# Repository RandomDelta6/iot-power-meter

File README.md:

# Iot Enabled Power Meter
Client server model for real-time monitoring of power usage aimed to simplify and modernise power usage readings and subsequent billing. Server backend handled by Firebase and Frontend made as a dynamic web app with angular framework. This project aims to elevate the process of power metering to modern connected standards and is primarily aimed towards power utility companies such that they may modernise their metering devices and enable them to be connected to the internet, allowing realtime monitoring and other advanced features like automated billing, remote disconnection, power outage detection and much more!  
The primary focus points of this project is simplicity, ease of installation of module, cost efficiency and rich user experience. 

## Documentation:
Slideshow presentation of the project highlighting the prominent topics discussed is available [here](https://docs.google.com/presentation/d/1crQ9AChwzRSzLb8-jiRmHGEgWye28_40_jXuga4SWwA/edit?usp=sharing).  
The [documentation](https://docs.google.com/document/d/1vDl4VJHqPTy9oJ1By9j4uT5io9Db-l0d9iFhtp2ZmS8/edit?usp=sharing) for the research conducted and subsequent issues addressed has been made available.  
[Dataflow logic](https://whimsical.com/data-flow-XnRbm9PbMYaVgHn5g6pd81) and [Firmware Algorithm Logic](https://whimsical.com/firmware-algorithm-PJ4HBDd6Cb4NwG5o3SaENn) flowcharts are also provided.  
Short Infographic video showcasing the project and primary discussion points is available [here](https://www.youtube.com/watch?v=jMkZ5F2Xh4k).

## Folder Structure:
```
./
  |-- power-iot-meter-fe (the frontend dashboard)
  --- power-iot-meter-hw (the firmware sketch)
```

## Frontend Preview

## Tools used:
- Angular
- Platform IO
- Espressif ESP32
- Arduino Framework
- Firebase RTDB
- Firebase Auth
- KiCAD

## Languages Used: 
- C/C++
- JS/TS

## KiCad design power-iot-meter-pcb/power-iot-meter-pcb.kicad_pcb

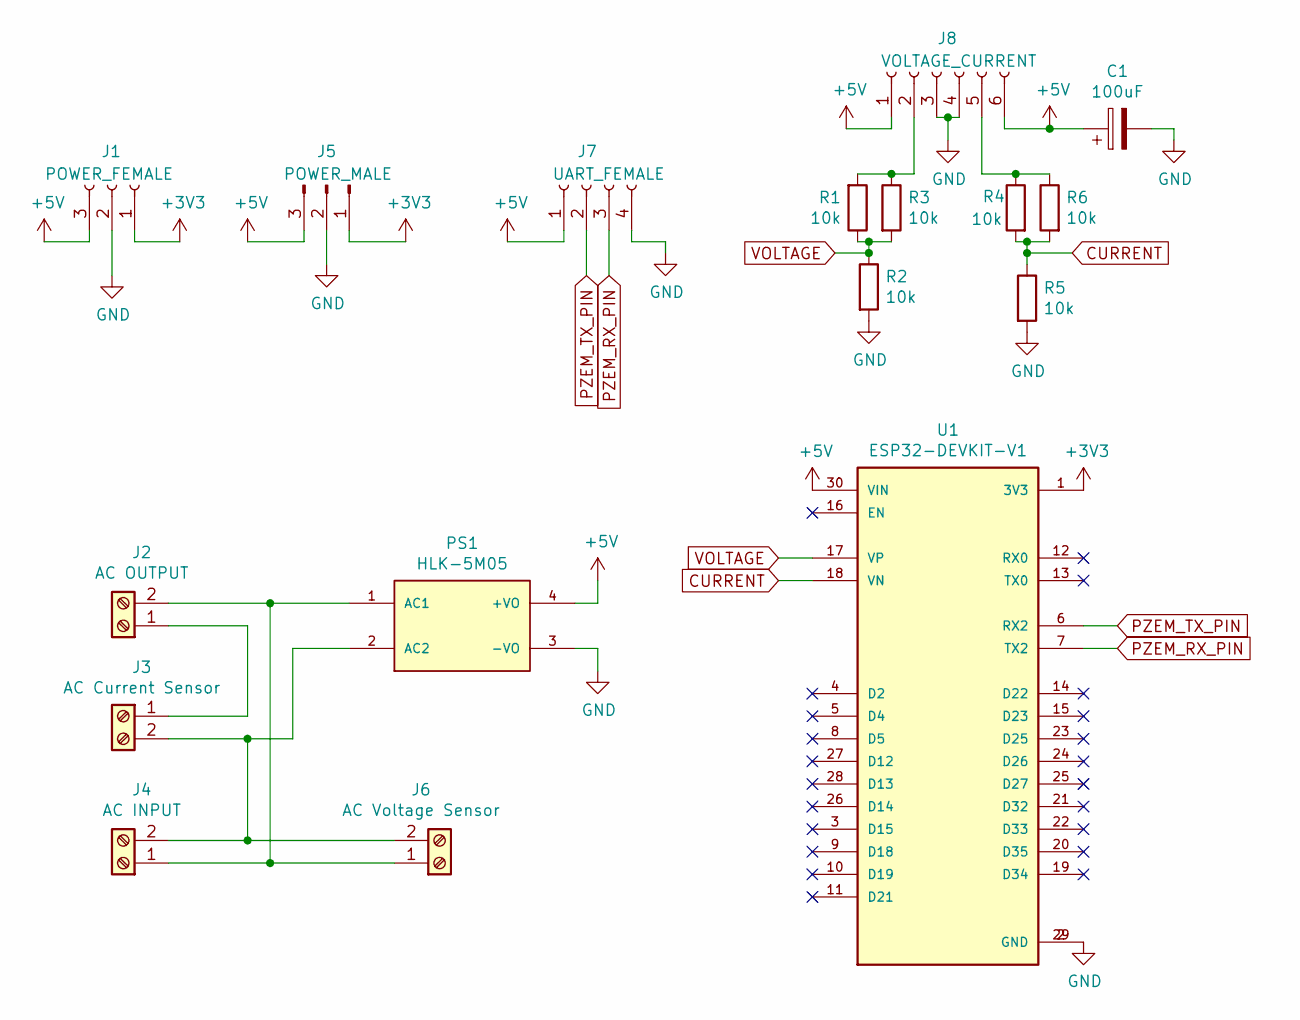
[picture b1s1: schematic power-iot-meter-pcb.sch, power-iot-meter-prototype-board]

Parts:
C1: 100uF; CP_Radial_D8.0mm_P3.50mm
J1: POWER_FEMALE; PinSocket_1x03_P2.00mm_Vertical
J2: AC OUTPUT; TerminalBlock_Altech_AK300-2_P5.00mm
J3: AC Current Sensor; SolderWire-0.5sqmm_1x02_P4.6mm_D0.9mm_OD2.1mm_Relief
J4: AC INPUT; TerminalBlock_Altech_AK300-2_P5.00mm
J5: POWER_MALE; PinHeader_1x03_P2.00mm_Vertical
J6: AC Voltage Sensor; SolderWire-0.5sqmm_1x02_P4.6mm_D0.9mm_OD2.1mm_Relief
J7: UART_FEMALE; PinSocket_1x04_P2.00mm_Vertical
J8: VOLTAGE_CURRENT; PinSocket_1x06_P2.00mm_Vertical
PS1: HLK-5M05; CONV_HLK-5M05; PARTREV N/A
R1, R2, R3, R4, R5, R6: 10k; R_Axial_DIN0207_L6.3mm_D2.5mm_P10.16mm_Horizontal
U1: ESP32-DEVKIT-V1; MODULE_ESP32_DEVKIT_V1; PARTREV N/A

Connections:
+3V3: J1.1, J5.1, U1.1 (3V3)
+5V: C1.1, J1.3, J5.3, J7.1, J8.1, J8.6, PS1.4 (+VO), U1.30 (VIN)
CURRENT: R4.2, R5.1, R6.2, U1.18 (VN)
GND: C1.2, J1.2, J5.2, J7.4, J8.3, J8.4, PS1.3 (-VO), R2.2, R5.2, U1.2 (GND), U1.29 (GND)
unnamed: J2.1, J3.1
unnamed: J2.2, J4.1, J6.1, PS1.1 (AC1)
unnamed: J3.2, J4.2, J6.2, PS1.2 (AC2)
unnamed: J8.2, R1.2, R3.1
unnamed: J8.5, R4.1, R6.1
PZEM_RX_PIN: J7.3, U1.7 (TX2)
PZEM_TX_PIN: J7.2, U1.6 (RX2)
VOLTAGE: R1.1, R2.1, R3.2, U1.17 (VP)

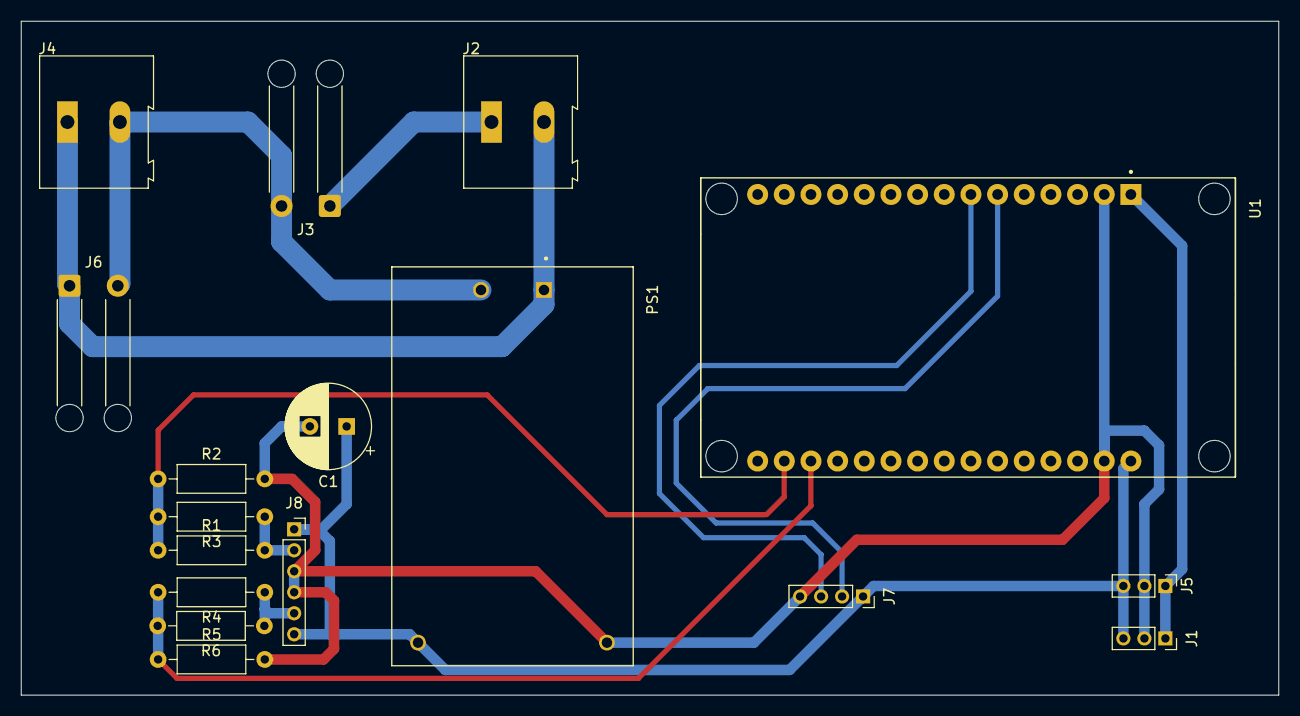
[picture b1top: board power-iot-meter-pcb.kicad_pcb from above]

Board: 2 copper layers, 119.8 x 64.2 mm, 17 parts (0 on the bottom side), 12 nets.

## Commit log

2023-06-29 added project documentation file
